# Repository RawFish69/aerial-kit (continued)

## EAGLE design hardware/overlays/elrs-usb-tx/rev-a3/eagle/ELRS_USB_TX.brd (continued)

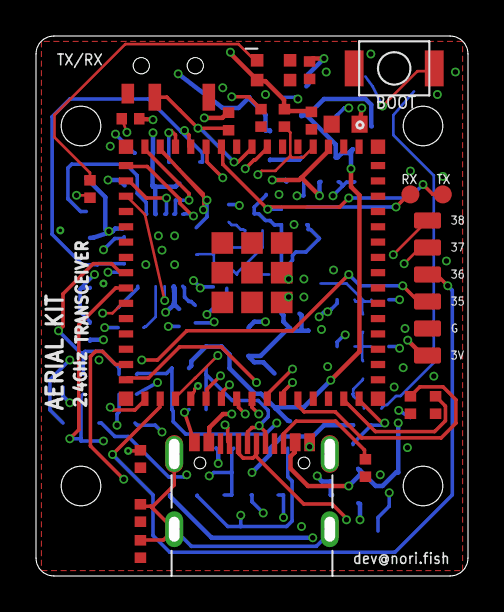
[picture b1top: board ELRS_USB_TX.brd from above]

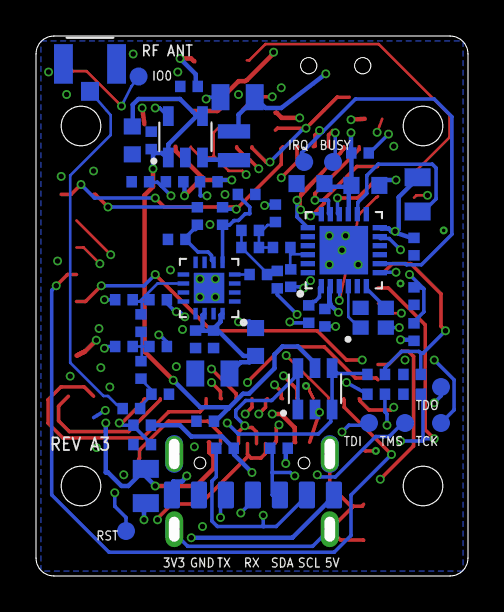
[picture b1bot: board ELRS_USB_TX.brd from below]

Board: 4 copper layers, 24.0 x 30.0 mm, 87 parts (65 on the bottom side), 60 nets.

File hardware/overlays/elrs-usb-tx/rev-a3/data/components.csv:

ref,schematic_value,pcb_value,device_set,device,footprint,x_mm,y_mm,rotation,side,population_designation
C1,100n,100n,C,0402,C0402,14.6,8.6,MR0,bottom,see assembly records
C10,100n,100n,C,0402,C0402,15.5,27.2,MR0,bottom,see assembly records
C11,4.7u,4.7u,C,0603,C0603,8.75,21.8,MR0,bottom,see assembly records
C12,22u,22u,C,0805,C0805,14.2,11.25,MR0,bottom,see assembly records
C13,10u,10u,C,0603,C0603,17.2,25.1,R0,top,see assembly records
C14,100n,100n,C,0402,C0402,15.3,25.3,R90,top,see assembly records
C19,1u,1u,C,0402,C0402,18.1,7.3,MR0,bottom,see assembly records
C2,4.7n DNP,4.7n DNP,C,0402,C0402,5.8,3.5,R90,top,DNP
C20,100n,100n,C,0402,C0402,15.2,28.1,R90,top,see assembly records
C21,10n,10n,C,0402,C0402,8.85,14.55,MR90,bottom,see assembly records
C22,10n,10n,C,0402,C0402,7.95,14.35,MR90,bottom,see assembly records
C23,470n,470n,C,0402,C0402,3,18.3,MR90,bottom,see assembly records
C24,100n,100n,C,0402,C0402,3,15.55,MR90,bottom,see assembly records
C25,100n,100n,C,0402,C0402,6,23.5,MR180,bottom,see assembly records
C26,0.8p,0.8p,C,0402,C0402,9.85,16.55,MR90,bottom,see assembly records
C27,1.2p,1.2p,C,0402,C0402,10.7,20.15,MR270,bottom,see assembly records
C28,0.5p,0.5p,C,0402,C0402,12.1,19.2,MR180,bottom,see assembly records
C29,1.2p,1.2p,C,0402,C0402,10.595,16.465,MR90,bottom,see assembly records
C3,12p DNP,12p DNP,C,0402,C0402,3.1,10.1,MR0,bottom,DNP
C30,100p,100p,C,0402,C0402,11.65,16.75,MR180,bottom,see assembly records
C31,1u,1u,C,0402,C0402,14.135,13.15,MR90,bottom,see assembly records
C32,220p,220p,C,0402,C0402,15.135,13.15,MR90,bottom,see assembly records
C33,0.3p,0.3p,C,0402,C0402,17.215,15.35,MR180,bottom,see assembly records
C34,1.5p,1.5p,C,0402,C0402,19.115,15.35,MR0,bottom,see assembly records
C35,1.5p,1.5p,C,0402,C0402,17.215,12.75,MR180,bottom,see assembly records
C36,1.5p,1.5p,C,0402,C0402,19.115,12.75,MR0,bottom,see assembly records
C37,1.5p,1.5p,C,0402,C0402,17.1,10.1,MR180,bottom,see assembly records
C4,12p DNP,12p DNP,C,0402,C0402,3.1,11.2,MR0,bottom,DNP
C6,4.7u,4.7u,C,0603,C0603,18.65,24.2,MR90,bottom,see assembly records
C7,100n,100n,C,0402,C0402,17.6,24.2,MR270,bottom,see assembly records
C8,6.8p,6.8p,C,0402,C0402,16.3,21.9,MR0,bottom,see assembly records
C9,22u,22u,C,0805,C0805,12.8,26.6,MR0,bottom,see assembly records
D1,USBLC6-2SC6,USBLC6-2SC6,USBLC6-2,SC6,SOT23-6,8.5,10.4,MR0,bottom,see assembly records
F1,0.5A hold,0.5A hold,PTC,0805,F0805,17.9,5,MR270,bottom,see assembly records
FB1,220R@100M,220R@100M,FB,0603,FB0603,5.7,21.7,MR180,bottom,see assembly records
FB2,220R@100M,220R@100M,FB,0603,FB0603,11.8,13,MR270,bottom,see assembly records
J1,USB4105-GF-A,USB4105-GF-A,USB_C,USB4105,USB4105_GF_A,12,0,R0,top,see assembly records
J2,U.FL-R-SMT-1,U.FL-R-SMT-1,UFL,,UFL_R_SMT,21,28.45,MR0,bottom,see assembly records
J3,UART/I2C + POWER,UART/I2C + POWER,HDR7,,PADS7_1P5,11.95,4.5,MR0,bottom,see assembly records
J5,GPIO 3V3/G/35/36/37/38,GPIO 3V3/G/35/36/37/38,HDR6,,PADS6_1P5,21.75,16,R90,top,see assembly records
L1,2.2uH,2.2uH,L,DFE201610,DFE201610,13,23.9,MR90,bottom,see assembly records
L2,15uH,15uH,L,0805,L0805,2.8,21.2,MR90,bottom,see assembly records
L3,3.0nH,3.0nH,L,0402,L0402,10.35,18.25,MR180,bottom,see assembly records
L4,2.5nH,2.5nH,L,0402,L0402,12.1,18.25,MR180,bottom,see assembly records
L5,2.4nH,2.4nH,L,0402,L0402,18.165,14.05,MR270,bottom,see assembly records
L6,2.4nH,2.4nH,L,0402,L0402,18.165,11.45,MR270,bottom,see assembly records
LED1,WS2812B-2020,WS2812B-2020,WS2812B,2020,LED2020_WS2812B,13.2,28.1,R0,top,see assembly records
R1,5.1k,5.1k,R,0402,R0402,5.8,6.5,R90,top,see assembly records
R10,100k,100k,R,0402,R0402,18.2,21.9,MR0,bottom,see assembly records
R11,10k,10k,R,0402,R0402,18.1,8.38,MR0,bottom,see assembly records
R12,10k,10k,R,0402,R0402,13.8,25.45,R90,top,see assembly records
R13,10k,10k,R,0402,R0402,20.8,9.5,R90,top,see assembly records
R14,10k,10k,R,0402,R0402,5.25,25.4,R0,top,see assembly records
R15,33R,33R,R,0402,R0402,3,21.5,R90,top,see assembly records
R16,0R,0R,R,0402,R0402,3,13.55,MR90,bottom,see assembly records
R17,1k,1k,R,0402,R0402,13.635,20,MR270,bottom,see assembly records
R18,1k,1k,R,0402,R0402,15.035,20,MR270,bottom,see assembly records
R19,100k,100k,R,0402,R0402,12.3,21.2,MR180,bottom,see assembly records
R2,5.1k,5.1k,R,0402,R0402,18.3,6,R90,top,see assembly records
R20,100k,100k,R,0402,R0402,16.185,18.7,MR0,bottom,see assembly records
R22,4.7k,4.7k,R,0402,R0402,10.5,7.1,MR0,bottom,see assembly records
R23,4.7k,4.7k,R,0402,R0402,13.5,7.1,MR0,bottom,see assembly records
R24,0R,0R,R,0402,R0402,18.7,9.3,MR180,bottom,see assembly records
R26,10k,10k,R,0402,R0402,10.7,25.25,R90,top,see assembly records
R27,10k,10k,R,0402,R0402,22.2,9.5,R90,top,see assembly records
R28,10k,10k,R,0402,R0402,12.5,25.45,R90,top,see assembly records
R3,0R,0R,R,0402,R0402,5.8,1.5,R90,top,see assembly records
R4,22R,22R,R,0402,R0402,5.1,10.1,MR0,bottom,see assembly records
R5,22R,22R,R,0402,R0402,5.1,11.2,MR0,bottom,see assembly records
R9,453k,453k,R,0402,R0402,14.4,21.9,MR0,bottom,see assembly records
SW1,BOOT/BIND,BOOT/BIND,SW,TS1088,SW_TS1088,19.9,28.2,R0,top,see assembly records
SW2,TX/RX ROLE,TX/RX ROLE,SW_SPDT,SSSS810701,SW_SSSS810701,7.35,28.35,R180,top,see assembly records
TP1,ESP_EN,ESP_EN,TP,,TP_1MM,19,2.5,MR0,bottom,see assembly records
TP10,JTAG_TMS,JTAG_TMS,TP,,TP_1MM,3.5,8.5,MR0,bottom,see assembly records
TP2,ESP_IO0,ESP_IO0,TP,,TP_1MM,18.3,27.75,MR0,bottom,see assembly records
TP3,JTAG_TDI,JTAG_TDI,TP,,TP_1MM,5.5,8.5,MR0,bottom,see assembly records
TP4,JTAG_TDO,JTAG_TDO,TP,,TP_1MM,1.5,10.5,MR0,bottom,see assembly records
TP5,PA_TXEN,PA_TXEN,TP,,TP_1MM,22.6,21.2,R0,top,see assembly records
TP6,PA_RXEN,PA_RXEN,TP,,TP_1MM,20.8,21.2,R0,top,see assembly records
TP7,RADIO_BUSY,RADIO_BUSY,TP,,TP_1MM,7.5,23,MR0,bottom,see assembly records
TP8,RADIO_DIO1,RADIO_DIO1,TP,,TP_1MM,9.1,23,MR0,bottom,see assembly records
TP9,JTAG_TCK,JTAG_TCK,TP,,TP_1MM,1.5,8.5,MR0,bottom,see assembly records
U2,TLV62569DBVR,TLV62569DBVR,TLV62569,DBV,SOT23-5,15.7,24.4,MR0,bottom,see assembly records
U3,ESP32-S3-MINI-1U-N8,ESP32-S3-MINI-1U-N8,ESP32-S3-MINI-1U,N8,ESP32_S3_MINI_1U,12,16.85,R270,top,see assembly records
U4,SX1280IMLTRT,SX1280IMLTRT,SX1280,,QFN24_4X4_SX1280,6.9,18.1,MR90,bottom,see assembly records
U5,RFX2401C,RFX2401C,RFX2401C,,QFN16_3X3_RFX2401C,14.385,16,MR180,bottom,see assembly records
Y1,52MHz 10pF,52MHz 10pF,XTAL,2016,XTAL2016_4P,5.265,14.35,MR0,bottom,see assembly records
